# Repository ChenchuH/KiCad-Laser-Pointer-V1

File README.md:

# KiCad-Laser-Pointer-V1
Laser Pointer V1 - A compact, hold-to-activate laser pointer designed in KiCad. 
Accepts a AAA battery, steps up voltage to a steady 3.3V to power a 5mW 650nm Red Adafruit laser module. 

Work in progress as of now.

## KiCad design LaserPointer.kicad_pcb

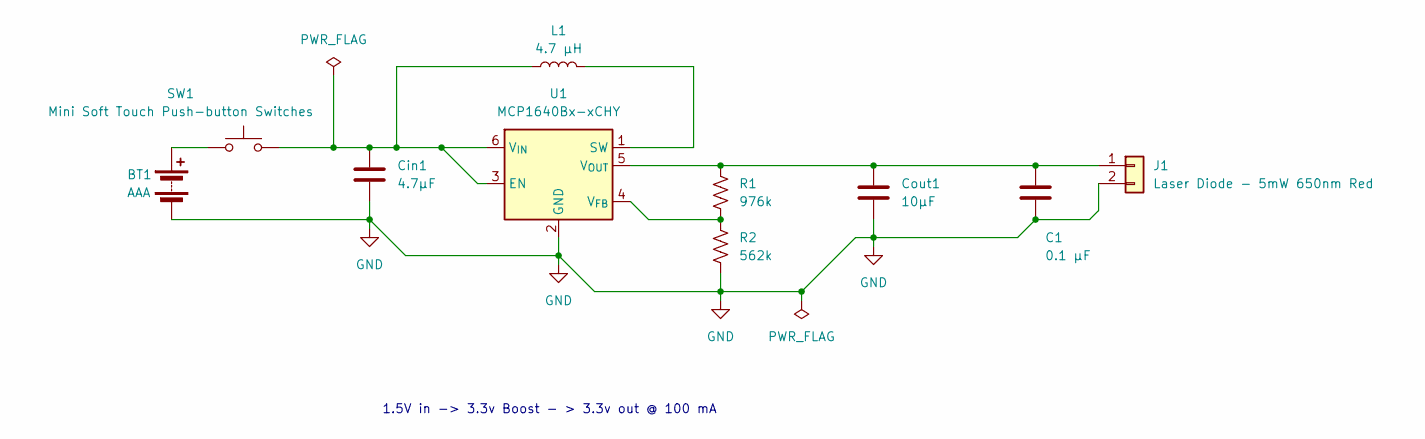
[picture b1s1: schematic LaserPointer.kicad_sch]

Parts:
BT1: AAA; Batt terminal pads
C1: 0.1 µF; C_0603_1608Metric
Cin1: 4.7µF; C_0805_2012Metric
Cout1: 10µF; C_0805_2012Metric
J1: Laser Diode - 5mW 650nm Red; Adafruit Laser Diode - 5mW 650nm Red
L1: 4.7 µH; L_1210_3225Metric
R1: 976k; R_0603_1608Metric
R2: 562k; R_0603_1608Metric
SW1: Mini Soft Touch Push-button Switches; SW_SPST_PTS645Sx43SMTR92
U1: MCP1640Bx-xCHY; SOT-23-6

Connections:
GND: BT1.2 (-), C1.2, Cin1.2, Cout1.2, J1.2, R2.2, U1.2 (GND)
unnamed: BT1.1 (+), SW1.1
unnamed: C1.1, Cout1.1, J1.1, R1.1, U1.5 (V_{OUT})
unnamed: Cin1.1, L1.1, SW1.2, U1.3 (EN), U1.6 (V_{IN})
unnamed: L1.2, U1.1 (SW)
unnamed: R1.2, R2.1, U1.4 (V_{FB})

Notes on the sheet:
1.5V in -> 3.3v Boost - > 3.3v out @ 100 mA

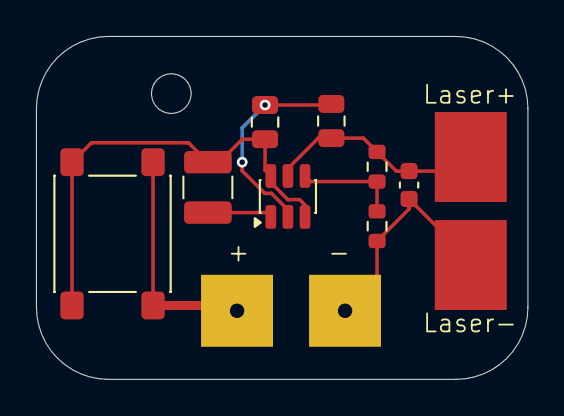
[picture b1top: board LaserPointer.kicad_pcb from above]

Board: 2 copper layers, 27.3 x 19.1 mm, 11 parts (0 on the bottom side), 6 nets.

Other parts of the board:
M2_1: MountingHole_2.2mm_M2
